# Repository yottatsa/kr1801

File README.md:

# KR1801 computer

KiCAD goodies to work with K1801VM1

[Documenation](https://yottatsa.github.io/kr1801/).

## К1801ВМ1 (K1801VM1)

KiCAD symbol and footprint, 3D model.

## Retrobrew EuroCard bus v6

KiCAD symbol with most of the pins in 16bit configuration (to be finished).

## KR1801VM1 ECB card

Minimal card that has clock and facilities to boot.

## Documentation sources

* [1801BM1/cpu11](https://github.com/1801BM1/cpu11/tree/6452c7d89c5c2e69dccbcec1f96eda947a3de05e/vm1/doc)
* [arktur04/1801VM1_docs](https://github.com/arktur04/1801VM1_docs)

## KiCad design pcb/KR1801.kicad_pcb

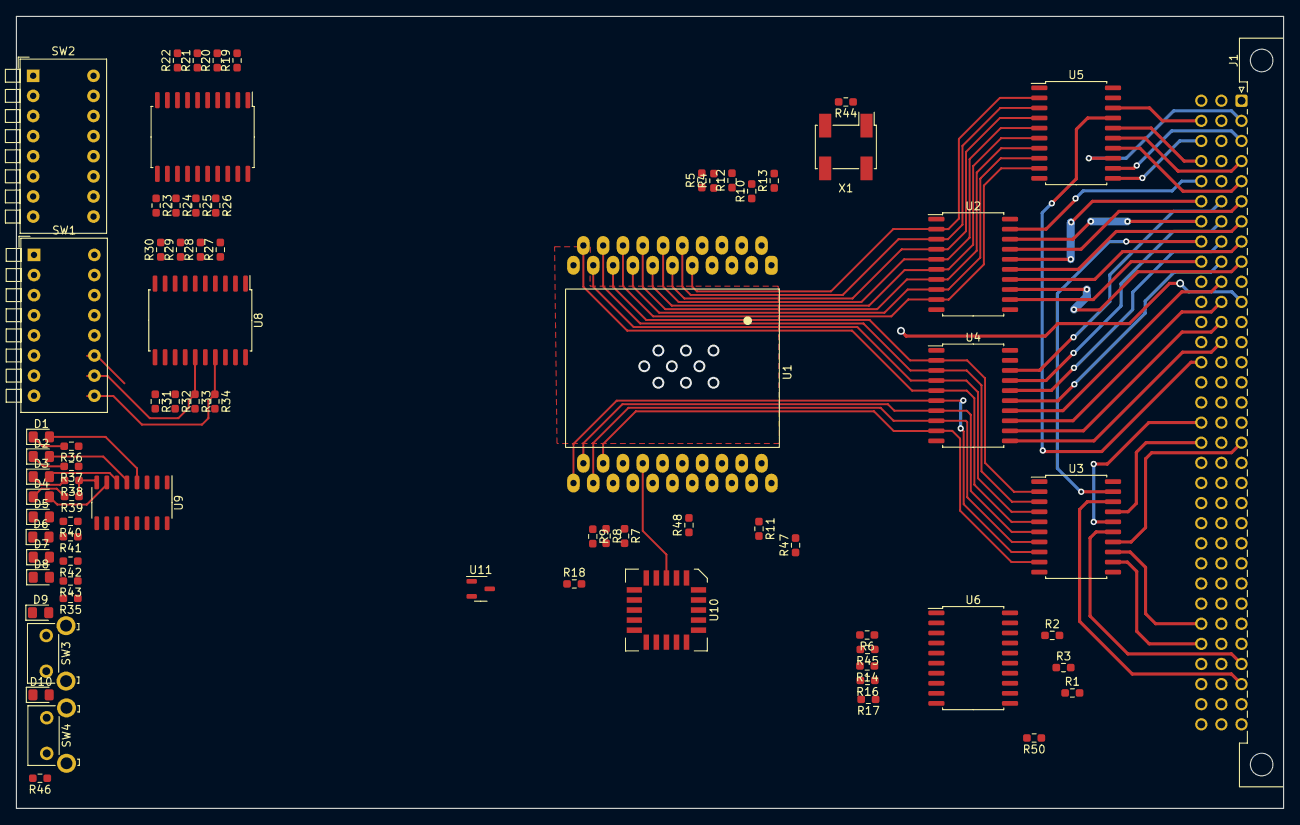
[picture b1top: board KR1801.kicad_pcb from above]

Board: 2 copper layers, 160.0 x 100.0 mm, 75 parts (0 on the bottom side), 128 nets.

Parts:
D1, D2, D3, D4, D5, D6, D7, D8: LED; LED_0805_2012Metric_Pad1.15x1.40mm_HandSolder
D9: DCLO; LED_0805_2012Metric_Pad1.15x1.40mm_HandSolder
D10: NMI; LED_0805_2012Metric_Pad1.15x1.40mm_HandSolder
J1: Eurocard UNIBUS; DIN41612_C_3x32_Male_Horizontal_THT
R1, R2, R6, R8, R9, R10, R16, R17, R18, R47, R50: 0R; R_0603_1608Metric_Pad0.98x0.95mm_HandSolder
R3, R4, R5, R7, R11, R12, R13, R14, R19, R20, R21, R22, R23, R24, R25, R26, R27, R28, R29, R30, R31, R32, R33, R34, R45: R; R_0603_1608Metric_Pad0.98x0.95mm_HandSolder
R35, R36, R37, R38, R39, R40, R41, R42, R43, R46: RLED; R_0603_1608Metric_Pad0.98x0.95mm_HandSolder
R44: NPR; R_0603_1608Metric_Pad0.98x0.95mm_HandSolder
R48: WEAKR; R_0603_1608Metric_Pad0.98x0.95mm_HandSolder
SW1: Reset Vector; SW_DIP_SPSTx08_Piano_10.8x21.88mm_W7.62mm_P2.54mm
SW2: Opts; SW_DIP_SPSTx08_Piano_10.8x21.88mm_W7.62mm_P2.54mm
SW3: NMI; SW_SPST_Omron_B3F-315x_Angled
SW4: RESET; SW_SPST_Omron_B3F-315x_Angled
U1: К1801ВМ1; 2204.42
U2, U3: 74HC564; SOIC-20W_7.5x12.8mm_P1.27mm
U4, U5: 74HC640; SOIC-20W_7.5x12.8mm_P1.27mm
U6: 74AHC273; SOIC-20W_7.5x12.8mm_P1.27mm
U7, U8: 74LS240; SOIC-20W_7.5x12.8mm_P1.27mm
U9: 74LS259; SO-16_3.9x9.9mm_P1.27mm
U10: GAL16V8; PLCC-20
U11: MCP100-475D; SOT-23-3
X1: Oscillator_SMD_Fordahl_DFAS2-4Pin_7.3x5.1mm_HandSoldering

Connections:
A0: J1.c5 (A0), U2.19 (Q0)
A1: J1.c7 (A1), U2.18 (Q1)
A2: J1.a6 (A2), U2.17 (Q2)
A3: J1.c6 (A3), U2.16 (Q3)
A4: J1.a7 (A4), U2.15 (Q4)
A5: J1.a8 (A5), U2.14 (Q5)
A6: J1.a9 (A6), U2.13 (Q6)
A7: J1.c9 (A7), U2.12 (Q7)
A8: J1.c8 (A8), U3.19 (Q0)
A9: J1.a30 (A9), U3.18 (Q1)
A10: J1.c18 (A10), U3.17 (Q2)
A11: J1.c17 (A11), U3.16 (Q3)
A12: J1.c27 (A12), U3.13 (Q6)
A13: J1.a29 (A13), U3.15 (Q4)
A14: J1.a18 (A14), U3.14 (Q5)
A15: J1.c28 (A15), U3.12 (Q7)
AD0: U1.9 (~AD0), U2.2 (D0), U5.2 (A0), U7.18 (O0a)
AD1: U1.10 (~AD1), U2.3 (D1), U5.3 (A1), U7.16 (O1a)
AD2: U1.11 (~AD2), U2.4 (D2), U5.4 (A2), U7.14 (O2a)
AD3: U1.12 (~AD3), U2.5 (D3), U5.5 (A3), U7.12 (O3a)
AD4: U1.13 (~AD4), U2.6 (D4), U5.6 (A4), U7.9 (O0b)
AD5: U1.14 (~AD5), U2.7 (D5), U5.7 (A5), U7.7 (O1b)
AD6: U1.15 (~AD6), U2.8 (D6), U5.8 (A6), U7.5 (O2b)
AD7: U1.16 (~AD7), U2.9 (D7), U5.9 (A7), U7.3 (O3b)
AD8: U1.17 (~AD8), U3.2 (D0), U4.2 (A0), U8.18 (O0a)
AD9: U1.18 (~AD9), U3.3 (D1), U4.3 (A1), U8.16 (O1a)
AD10: U1.19 (~AD10), U3.4 (D2), U4.4 (A2), U8.14 (O2a)
AD11: U1.20 (~AD11), U3.5 (D3), U4.5 (A3), U8.12 (O3a)
AD12: U1.22 (~AD12), U3.8 (D6), U4.6 (A4), U8.9 (O0b), U9.13 (D)
AD13: U1.23 (~AD13), U3.6 (D4), U4.7 (A5), U8.7 (O1b), U9.1 (A0)
AD14: U1.24 (~AD14), U3.7 (D5), U4.8 (A6), U8.5 (O2b), U9.2 (A1)
AD15: U1.25 (~AD15), U3.9 (D7), U4.9 (A7), U8.3 (O3b), U9.3 (A2)
ALE: U2.11 (Load), U3.11 (Load), U10.12 (IO8)
CLC: J1.c29 (CLC), U1.1 (CLC), U6.11 (Cp), U10.1 (I1/CLK), X1.3 (OUT)
DB0: J1.c2 (D0), U5.18 (B0)
DB1: J1.c14 (D1), U5.17 (B1)
DB2: J1.c4 (D2), U5.16 (B2)
DB3: J1.a4 (D3), U5.15 (B3)
DB4: J1.a5 (D4), U5.14 (B4)
DB5: J1.a2 (D5), U5.13 (B5)
DB6: J1.a3 (D6), U5.12 (B6)
DB7: J1.c3 (D7), U5.11 (B7)
DB8: J1.b6 (D8), U4.18 (B0)
DB9: J1.b7 (D9), U4.17 (B1)
DB10: J1.b8 (D10), U4.16 (B2)
DB11: J1.b9 (D11), U4.15 (B3)
DB12: J1.b10 (D12), U4.14 (B4)
DB13: J1.b11 (D13), U4.13 (B5)
DB14: J1.b12 (D14), U4.12 (B6)
DB15: J1.b13 (D15), U4.11 (B7)
DR0: R19.1, SW2.16, U7.2 (I0a)
DR1: R20.1, SW2.15, U7.4 (I1a)
DR2: R21.1, SW2.14, U7.6 (I2a)
DR3: R22.1, SW2.13, U7.8 (I3a)
DR4: R23.1, SW2.12, U7.11 (I0b)
DR5: R24.1, SW2.11, U7.13 (I1b)
DR6: R25.1, SW2.10, U7.15 (I2b)
DR7: R26.1, SW2.9, U7.17 (I3b)
DR8: R27.1, SW1.16, U8.2 (I0a)
DR9: R28.1, SW1.15, U8.4 (I1a)
DR10: R29.1, SW1.14, U8.6 (I2a)
DR11: R30.1, SW1.13, U8.8 (I3a)
DR12: R31.1, SW1.12, U8.11 (I0b)
DR13: R32.1, SW1.11, U8.13 (I1b)
DR14: R33.1, SW1.10, U8.15 (I2b)
DR15: R34.1, SW1.9, U8.17 (I3b)
DT/~R: J1.c24 (~RD), U1.38 (~DIN), U4.1 (A->B), U5.1 (A->B), U7.19 (OEb), U8.19 (OEb), U10.2 (I2)
FAIL.LED: D9.2 (A), U10.13 (IO7)
GND: J1.a32 (GND), J1.b32 (GND), J1.c32 (GND), R35.1, R36.1, R37.1, R38.1, R39.1, R40.1, R41.1, R42.1, R43.1, R44.2, R46.1, SW1.1, SW1.2, SW1.3, SW1.4, SW1.5, SW1.6, SW1.7, SW1.8, SW2.1, SW2.2, SW2.3, SW2.4, SW2.5, SW2.6, SW2.7, SW2.8, SW3.1, SW4.1, U1.21 (GND), U2.10 (GND), U3.10 (GND), U4.10 (GND), U5.10 (GND), U6.10 (GND), U7.10 (GND), U8.10 (GND), U9.8 (GND), U10.10 (GND), U10.11 (I10/~OE), U11.3 (VSS), X1.2 (GND)
NMI.BTN: SW3.2, U10.7 (I7)
NMI.LED: D10.2 (A), U10.14 (IO6)
unnamed: D1.2 (A), U9.4 (Q0)
unnamed: D1.1 (K), R36.2
unnamed: D2.2 (A), U9.5 (Q1)
unnamed: D2.1 (K), R37.2
unnamed: D3.2 (A), U9.6 (Q2)
unnamed: D3.1 (K), R38.2
unnamed: D4.2 (A), U9.7 (Q3)
unnamed: D4.1 (K), R39.2
unnamed: D5.2 (A), U9.9 (Q4)
unnamed: D5.1 (K), R40.2
unnamed: D6.2 (A), U9.10 (Q5)
unnamed: D6.1 (K), R41.2
unnamed: D7.2 (A), U9.11 (Q6)
unnamed: D7.1 (K), R42.2
unnamed: D8.2 (A), U9.12 (Q7)
unnamed: D8.1 (K), R43.2
unnamed: D9.1 (K), R35.2
unnamed: D10.1 (K), R46.2
unnamed: J1.b28 (~DS0), R18.1
unnamed: J1.b29 (~DS1), R50.1
unnamed: R10.1, U1.3 (~DMGI)
unnamed: R8.1, U1.27 (~PA0)
unnamed: R9.1, U1.26 (~PA1)
unnamed: R16.1, U6.7 (D2)
unnamed: R17.1, U6.8 (D3)
unnamed: R1.1, U6.13 (D4)
unnamed: R2.1, U6.17 (D6)
unnamed: R47.1, U10.4 (I4)
unnamed: R6.2, U10.16 (IO4)
unnamed: R48.2, U10.15 (IO5)
unnamed: R44.1, X1.1 (OE)
VCC: J1.a1 (VCC), J1.b1 (VCC), J1.c1 (VCC), R1.2, R2.2, R3.2, R4.2, R5.2, R7.2, R8.2, R9.2, R10.2, R11.2, R12.2, R13.2, R14.2, R16.2, R17.2, R19.2, R20.2, R21.2, R22.2, R23.2, R24.2, R25.2, R26.2, R27.2, R28.2, R29.2, R30.2, R31.2, R32.2, R33.2, R34.2, R45.2, U1.42 (VCC), U2.20 (VCC), U3.20 (VCC), U4.20 (VCC), U5.20 (VCC), U6.20 (VCC), U7.20 (VCC), U8.20 (VCC), U9.16 (VCC), U10.20 (VCC), U11.2 (VDD), X1.4 (Vcc)
~ACLO: U1.30 (~ACLO), U6.2 (Q0)
~ALE: R11.1, R18.2, U1.41 (~SYNC), U10.9 (I9)
~BEN: R7.1, U1.28 (~BSY), U2.1 (OE), U3.1 (OE), U10.8 (I8)
~DCLO: J1.c31 (~RESET), SW4.2, U1.29 (~DCLO), U6.1 (~Mr), U9.15 (Clr), U10.6 (I6), U11.1 (~RST)
~DEN: U4.19 (CE), U5.19 (CE), U10.17 (I03)
~DMGO: J1.a31 (~BUSAK), U1.4 (~DMGO)
~DMR: J1.a11 (~BUSRQ), R12.1, U1.5 (~DMR)
~DOUT: J1.c22 (~WR), U1.37 (~DOUT), U10.3 (I3)
~DS1: R50.2, U10.18 (IO2)
~HALT: J1.c25 (~HALT), R14.1, U6.4 (D1)
~IAKO: J1.b25 (~INTA), U1.36 (~IAKO)
~INIT: J1.c26 (~RESOUT), R48.1, U1.34 (~INIT)
~IRQ1: U1.31 (~IRQ1), U6.5 (Q1)
~IRQ2: U1.32 (IRQ2), U6.6 (Q2)
~IRQ3: U1.33 (IRQ3), U6.9 (Q3)
~LED: U9.14 (E), U10.19 (IO1)
~NMI: J1.c20 (~NMI), R6.1, R45.1, U6.3 (D0)
~RDY: J1.a22 (~RDY), R3.1, U6.14 (D5)
~RPLY: U1.39 (~RPLY), U6.15 (Q5)
~SACK: R13.1, U1.2 (~SACK)
~SEL1: R4.1, R47.2, U1.7 (~SEL1), U8.1 (OEa)
~SEL2: R5.1, U1.8 (~SEL2)
~SP: U1.6 (~SP), U6.16 (Q6)
~VIRQ: J1.c21 (~INT), U1.35 (VIRQ), U6.12 (Q4)
~WTBT: U1.40 (~WTBT), U10.5 (I5)

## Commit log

2023-11-09 docs
2023-11-09 initial KiCAD commit
2023-11-09 3D models
2023-11-10 more docs and boot
2023-11-10 random placement test
2023-11-10 most of the glue logic and controls
2023-11-12 final logic, gal, 3D
2023-11-14 /init
2023-11-14 full? schematics
2023-11-16 placement/routing
